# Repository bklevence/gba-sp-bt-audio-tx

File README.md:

GBA SP Bluetooth Audio Transmitter
===========

Parts needed
-------------------
* GBA SP plug/audio cable sourced from: ([GBA SP Audio Adapter](https://en.wikipedia.org/wiki/Game_Boy_Advance_SP#/media/File:Nintendo-Game-Boy-Advance-Headphone-Adapter.jpg))
* GBA Link Plug, need to de-solder from one of the following: ([Link Cable](https://en.m.wikipedia.org/wiki/GameCube_%E2%80%93_Game_Boy_Advance_link_cable) | [Wireless Adapter](https://en.m.wikipedia.org/wiki/Game_Boy_Advance_Wireless_Adapter))
* DIY bt audio module: ([4.1 BT Transmitter Module, KCX_BT_EMITTER 5V](https://www.aliexpress.com/item/33058710334.html?spm=a2g0s.9042311.0.0.52ea4c4dOgsJLK) | [Need to find Aipods compatible version](about:blank))
* PCB made diy or eventually osh park...

Find the cheapest plug you can via GBA-GB link cable, I have not tried taking apart a link cable to scavenge those plugs, I am not sure if they will have PCB through hole pins. Using Wireless Adapters can get expensive unless you want to use the larger case!

You can find tons of SP audio cables on eBay for cheap.

Repository Contents
-------------------
* **/Eagle Files** - Eagle Project, board and schematic

Links/Sources
-------------------
* [/r/Gameboy](https://www.reddit.com/r/Gameboy/)
* [Gameboy Advance Headphone Jack Mods](https://github.com/rorosaurus/gba-sp-headphone-jack)
* [/u/mmaxeator's intermal bt mod](https://web.archive.org/web/20201025163111/https://mmax.tech/?p=3895&lang=en)
* [Newer internal, need to find better adapter like this](https://www.reddit.com/r/Gameboy/comments/pwfgdh/update_ags001_unhinged_sp_bluetooth_mod_for/)
* [something like this may work](https://www.aliexpress.com/item/1005001764137150.html?spm=a2g0o.productlist.0.0.45955e42yAVyGd&algo_pvid=224b6ea4-3445-40f3-a414-e6287c7ee70a&algo_exp_id=224b6ea4-3445-40f3-a414-e6287c7ee70a-1&pdp_ext_f=%7B%22sku_id%22%3A%2212000017705120581%22%7D&pdp_pi=-1%3B29.99%3B-1%3B-1%40salePrice%3BUSD%3Bsearch-mainSearch)

toDo
-------------------
* better traces for mill for bt_tx pcb
* find bt_tx that works with airpods
* fit whole circuit in GBA wireless adapter?
* 3D model casing for circuit?

brief history
-------------------
There have been many posts on reddit of people doing similar stuff, I'm just trying to compile what I've learned contacting others and seeing what people are doing in the modding community.

people
-------------------
* bk brandonklevence@gmail.com

License Information
-------------------
The hardware is released under [Creative Commons Share-alike 3.0](http://creativecommons.org/licenses/by-sa/3.0/).
All other code is open source hardware so please feel free to do anything you want with it;
you buy me a beer if you use this and we meet someday ([Beerware license](http://en.wikipedia.org/wiki/Beerware)).

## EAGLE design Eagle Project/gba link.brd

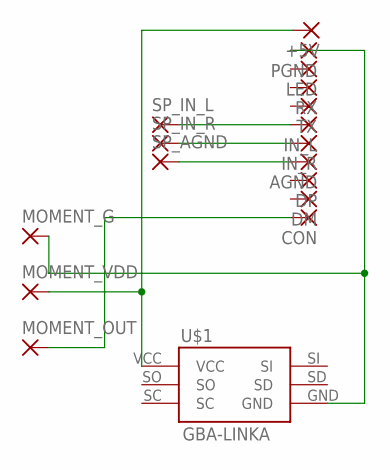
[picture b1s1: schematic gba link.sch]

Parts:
+5V: SMD2; SMD1,27-2,54
AGND: SMD2; SMD1,27-2,54
CON: SMD2; SMD1,27-2,54
DM: SMD2; SMD1,27-2,54
DP: SMD2; SMD1,27-2,54
IN_L: SMD2; SMD1,27-2,54
IN_R: SMD2; SMD1,27-2,54
LED: SMD2; SMD1,27-2,54
MOMENT_G: 2,15/1,0
MOMENT_OUT: 2,15/1,0
MOMENT_VDD: 2,15/1,0
PGND: SMD2; SMD1,27-2,54
RX: SMD2; SMD1,27-2,54
SP_AGND: 2,15/1,0
SP_IN_L: 2,15/1,0
SP_IN_R: 2,15/1,0
TX: SMD2; SMD1,27-2,54
U$1: GBA-LINKA; GBA-LINK-ALT

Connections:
unnamed: +5V.1, MOMENT_VDD.1, U$1.VCC
unnamed: MOMENT_G.1, PGND.1, U$1.GND
unnamed: AGND.1, SP_AGND.1
unnamed: IN_R.1, SP_IN_R.1
unnamed: IN_L.1, SP_IN_L.1
unnamed: CON.1, MOMENT_OUT.1

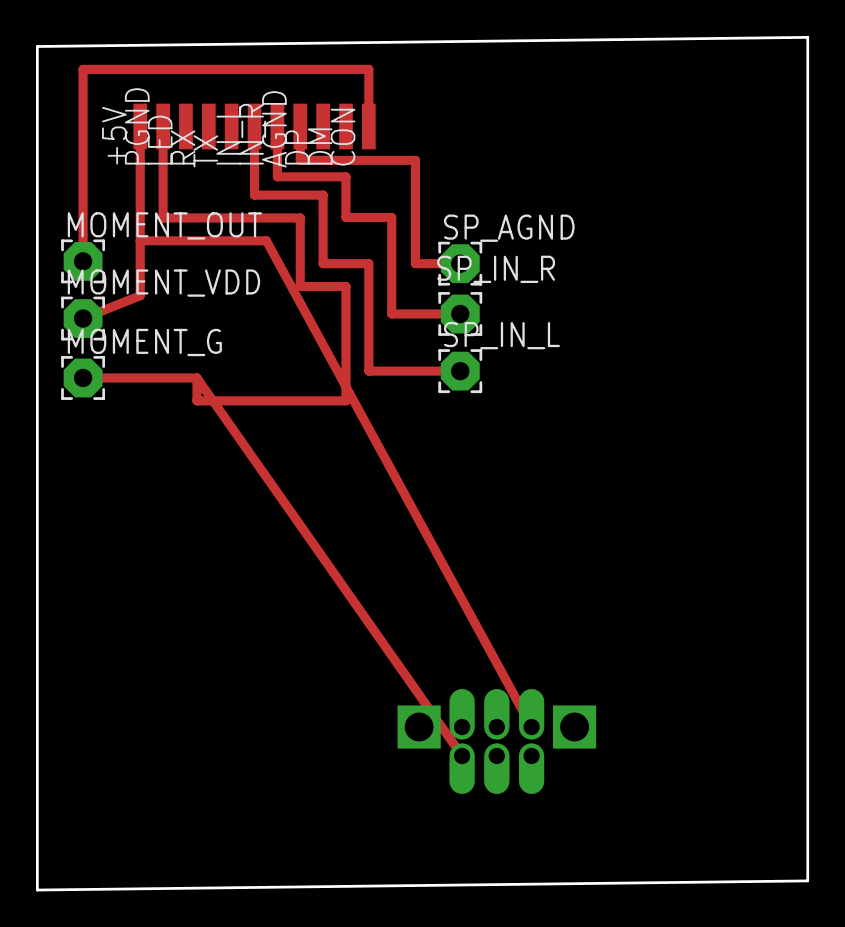
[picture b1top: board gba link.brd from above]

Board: 2 copper layers, 42.8 x 47.4 mm, 18 parts (0 on the bottom side), 6 nets.

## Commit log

2020-10-25 Eagle Files
2020-10-28 KiCad Start
2020-11-22 schematicmarkup.jpeg
